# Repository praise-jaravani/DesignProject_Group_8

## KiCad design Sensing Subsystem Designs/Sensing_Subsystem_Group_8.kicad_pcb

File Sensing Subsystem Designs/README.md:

# Sensing Subsystem Designs - Micro-Mouse Project

## Overview
This directory contains all the necessary design files for the Sensing Subsystem of the Micro-Mouse Project. It includes PCB design files, production resources such as bill of materials (BOM) and Gerber files for manufacturing the final design. The purpose of this subsystem is to enable the micro-mouse to detect obstacles within the maze environment effectively.

## File Structure

### `/Sensing Subsystem Designs/`
- **README.md**: This document, detailing the file structure and purpose of each item.
- **Sensing_Subsystem_Group_8.kicad_pcb**: KiCad PCB design file for the sensing subsystem.
- **Sensing_Subsystem_Group_8.kicad_prl**: KiCad project local file, storing project-specific settings.
- **Sensing_Subsystem_Group_8.kicad_pro**: KiCad project file, which contains setup and configuration for the sensing subsystem project.
- **Sensing_Subsystem_Group_8.kicad_sch**: KiCad schematic file for the sensing subsystem.
- **sym-lib-table**: KiCad symbol library table file, listing all symbol libraries used in the project.

### `/Production Resources/`
- Contains BOM and Gerber files necessary for the production of the sensing subsystem. These are critical for manufacturing and assembly of the designed PCB.

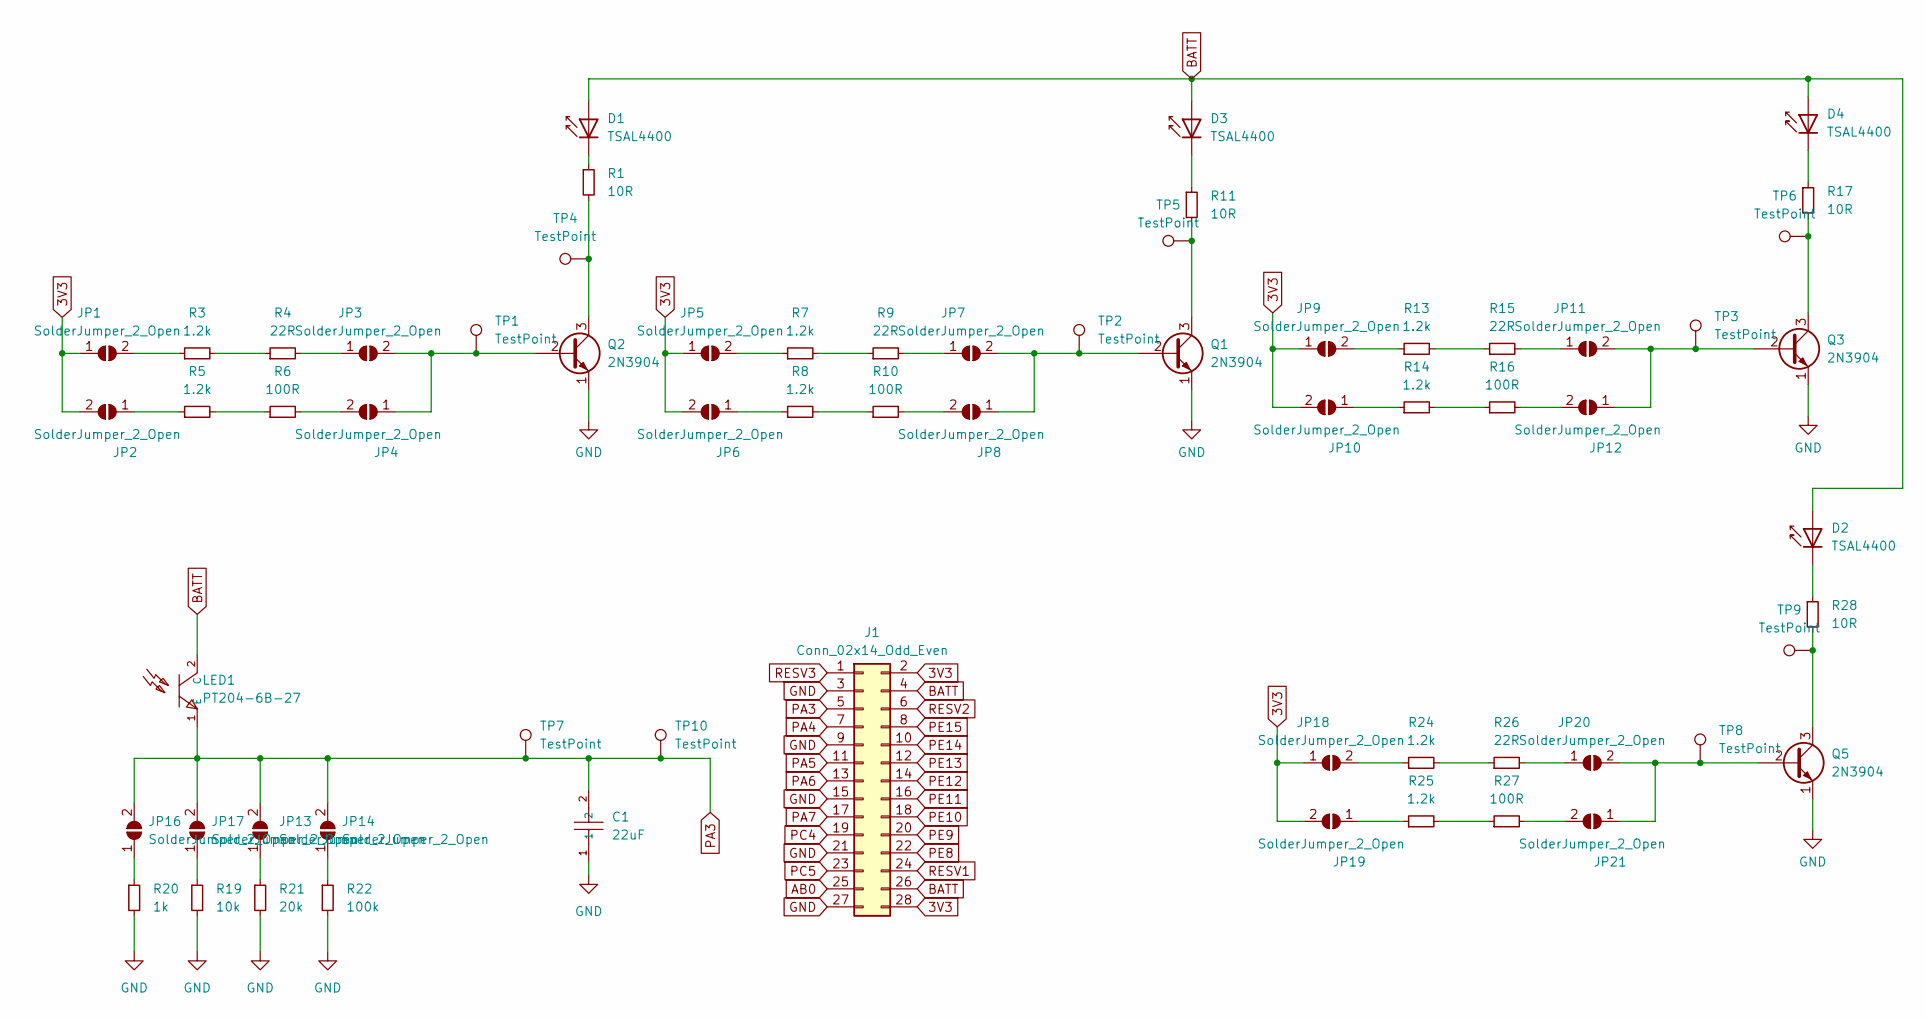
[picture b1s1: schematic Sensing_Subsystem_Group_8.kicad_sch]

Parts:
C1: 22uF; C0805; LCSC C45783
D1, D2, D3, D4: TSAL4400; LED_D3.0mm_IRBlack
J1: Conn_02x14_Odd_Even; PinHeader_2x14_P2.54mm_Vertical
JP1, JP2, JP3, JP4, JP5, JP6, JP7, JP8, JP9, JP10, JP11, JP12, JP13, JP14, JP16, JP17, JP18, JP19, JP20, JP21: SolderJumper_2_Open; SolderJumper-2_P1.3mm_Bridged2Bar_Pad1.0x1.5mm
LED1: PT204-6B-27; LED-TH_BD4.0-P2.54-RD; LCSC C142324
Q1, Q2, Q3, Q5: 2N3904; TO-92_Inline
R1, R11, R17, R28: 10R; R_0201_0603Metric
R3, R5, R7, R8, R13, R14, R24, R25: 1.2k; R_0201_0603Metric
R4, R9, R15, R26: 22R; R_0201_0603Metric
R6, R10, R16, R27: 100R; R_0201_0603Metric
R19: 10k; R_0201_0603Metric
R20: 1k; R_0201_0603Metric
R21: 20k; R_0201_0603Metric
R22: 100k; R_0201_0603Metric
TP1, TP2, TP3, TP4, TP5, TP6, TP7, TP8, TP9, TP10: TestPoint; TestPoint_2Pads_Pitch2.54mm_Drill0.8mm

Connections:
3V3: J1.2, J1.28, JP1.1 (A), JP2.2 (B), JP5.1 (A), JP6.2 (B), JP9.1 (A), JP10.2 (B), JP18.1 (A), JP19.2 (B)
AB0: J1.25
BATT: D1.2 (A), D2.2 (A), D3.2 (A), D4.2 (A), J1.4, J1.26, LED1.2 (C)
GND: C1.1, J1.3, J1.9, J1.15, J1.21, J1.27, Q1.1 (E), Q2.1 (E), Q3.1 (E), Q5.1 (E), R19.2, R20.2, R21.2, R22.2
unnamed: D1.1 (K), R1.1
unnamed: D2.1 (K), R28.1
unnamed: D3.1 (K), R11.1
unnamed: D4.1 (K), R17.1
unnamed: JP1.2 (B), R3.1
unnamed: JP2.1 (A), R5.1
unnamed: JP3.1 (A), R4.2
unnamed: JP3.2 (B), JP4.1 (A), Q2.2 (B), TP1.1
unnamed: JP4.2 (B), R6.2
unnamed: JP5.2 (B), R7.1
unnamed: JP6.1 (A), R8.1
unnamed: JP7.1 (A), R9.2
unnamed: JP7.2 (B), JP8.1 (A), Q1.2 (B), TP2.1
unnamed: JP8.2 (B), R10.2
unnamed: JP9.2 (B), R13.1
unnamed: JP10.1 (A), R14.1
unnamed: JP11.1 (A), R15.2
unnamed: JP11.2 (B), JP12.1 (A), Q3.2 (B), TP3.1
unnamed: JP12.2 (B), R16.2
unnamed: JP13.1 (A), R21.1
unnamed: JP14.1 (A), R22.1
unnamed: JP16.1 (A), R20.1
unnamed: JP17.1 (A), R19.1
unnamed: JP18.2 (B), R24.1
unnamed: JP19.1 (A), R25.1
unnamed: JP20.1 (A), R26.2
unnamed: JP20.2 (B), JP21.1 (A), Q5.2 (B), TP8.1
unnamed: JP21.2 (B), R27.2
unnamed: Q1.3 (C), R11.2, TP5.1
unnamed: Q2.3 (C), R1.2, TP4.1
unnamed: Q3.3 (C), R17.2, TP6.1
unnamed: Q5.3 (C), R28.2, TP9.1
unnamed: R3.2, R4.1
unnamed: R5.2, R6.1
unnamed: R7.2, R9.1
unnamed: R8.2, R10.1
unnamed: R13.2, R15.1
unnamed: R14.2, R16.1
unnamed: R24.2, R26.1
unnamed: R25.2, R27.1
PA3: C1.2, J1.5, JP13.2 (B), JP14.2 (B), JP16.2 (B), JP17.2 (B), LED1.1 (E), TP7.1, TP10.1
PA4: J1.7
PA5: J1.11
PA6: J1.13
PA7: J1.17
PC4: J1.19
PC5: J1.23
PE8: J1.22
PE9: J1.20
PE10: J1.18
PE11: J1.16
PE12: J1.14
PE13: J1.12
PE14: J1.10
PE15: J1.8
RESV1: J1.24
RESV2: J1.6
RESV3: J1.1

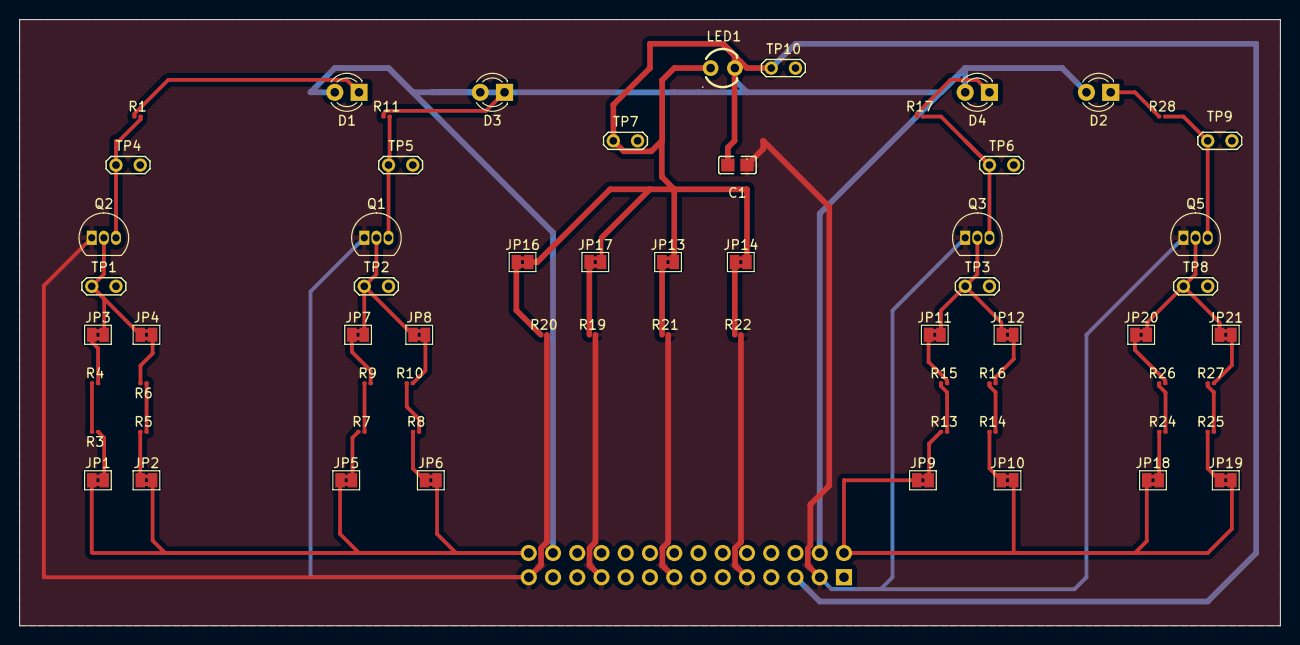
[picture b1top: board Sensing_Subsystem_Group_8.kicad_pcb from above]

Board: 2 copper layers, 132.1 x 63.5 mm, 65 parts (1 on the bottom side), 44 nets.

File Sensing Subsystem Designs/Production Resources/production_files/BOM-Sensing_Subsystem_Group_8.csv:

Comment,Designator,Footprint,LCSC
2N3904,"Q1,Q2,Q3,Q5",TO-92_Inline,C118538
PT204-6B-27,LED1,LED-TH_BD4.0-P2.54-RD,C142324
22uF,C1,C0805,C45783
TestPoint,TP9,TestPoint_2Pads_Pitch2.54mm_Drill0.8mm,
TestPoint,TP8,TestPoint_2Pads_Pitch2.54mm_Drill0.8mm,
10R,R28,R_0201_0603Metric,
100R,R27,R_0201_0603Metric,
22R,R26,R_0201_0603Metric,
1.2k,R25,R_0201_0603Metric,
1.2k,R24,R_0201_0603Metric,
SolderJumper_2_Open,JP21,SolderJumper-2_P1.3mm_Bridged2Bar_Pad1.0x1.5mm,
SolderJumper_2_Open,JP20,SolderJumper-2_P1.3mm_Bridged2Bar_Pad1.0x1.5mm,
SolderJumper_2_Open,JP19,SolderJumper-2_P1.3mm_Bridged2Bar_Pad1.0x1.5mm,
SolderJumper_2_Open,JP18,SolderJumper-2_P1.3mm_Bridged2Bar_Pad1.0x1.5mm,
TSAL4400,D2,LED_D3.0mm_IRBlack,
TestPoint,TP7,TestPoint_2Pads_Pitch2.54mm_Drill0.8mm,
TestPoint,TP6,TestPoint_2Pads_Pitch2.54mm_Drill0.8mm,
TestPoint,TP5,TestPoint_2Pads_Pitch2.54mm_Drill0.8mm,
TestPoint,TP4,TestPoint_2Pads_Pitch2.54mm_Drill0.8mm,
TestPoint,TP3,TestPoint_2Pads_Pitch2.54mm_Drill0.8mm,
TestPoint,TP2,TestPoint_2Pads_Pitch2.54mm_Drill0.8mm,
TestPoint,TP1,TestPoint_2Pads_Pitch2.54mm_Drill0.8mm,
100k,R22,R_0201_0603Metric,
20k,R21,R_0201_0603Metric,
1k,R20,R_0201_0603Metric,
10k,R19,R_0201_0603Metric,
10R,R17,R_0201_0603Metric,
100R,R16,R_0201_0603Metric,
22R,R15,R_0201_0603Metric,
1.2k,R14,R_0201_0603Metric,
1.2k,R13,R_0201_0603Metric,
10R,R11,R_0201_0603Metric,
100R,R10,R_0201_0603Metric,
22R,R9,R_0201_0603Metric,
1.2k,R8,R_0201_0603Metric,
1.2k,R7,R_0201_0603Metric,
100R,R6,R_0201_0603Metric,
1.2k,R5,R_0201_0603Metric,
22R,R4,R_0201_0603Metric,
1.2k,R3,R_0201_0603Metric,
10R,R1,R_0201_0603Metric,
SolderJumper_2_Open,JP17,SolderJumper-2_P1.3mm_Bridged2Bar_Pad1.0x1.5mm,
SolderJumper_2_Open,JP16,SolderJumper-2_P1.3mm_Bridged2Bar_Pad1.0x1.5mm,
SolderJumper_2_Open,JP14,SolderJumper-2_P1.3mm_Bridged2Bar_Pad1.0x1.5mm,
SolderJumper_2_Open,JP13,SolderJumper-2_P1.3mm_Bridged2Bar_Pad1.0x1.5mm,
SolderJumper_2_Open,JP12,SolderJumper-2_P1.3mm_Bridged2Bar_Pad1.0x1.5mm,
SolderJumper_2_Open,JP11,SolderJumper-2_P1.3mm_Bridged2Bar_Pad1.0x1.5mm,
SolderJumper_2_Open,JP10,SolderJumper-2_P1.3mm_Bridged2Bar_Pad1.0x1.5mm,
SolderJumper_2_Open,JP9,SolderJumper-2_P1.3mm_Bridged2Bar_Pad1.0x1.5mm,
SolderJumper_2_Open,JP8,SolderJumper-2_P1.3mm_Bridged2Bar_Pad1.0x1.5mm,
SolderJumper_2_Open,JP7,SolderJumper-2_P1.3mm_Bridged2Bar_Pad1.0x1.5mm,
SolderJumper_2_Open,JP6,SolderJumper-2_P1.3mm_Bridged2Bar_Pad1.0x1.5mm,
SolderJumper_2_Open,JP5,SolderJumper-2_P1.3mm_Bridged2Bar_Pad1.0x1.5mm,
SolderJumper_2_Open,JP4,SolderJumper-2_P1.3mm_Bridged2Bar_Pad1.0x1.5mm,
SolderJumper_2_Open,JP3,SolderJumper-2_P1.3mm_Bridged2Bar_Pad1.0x1.5mm,
SolderJumper_2_Open,JP2,SolderJumper-2_P1.3mm_Bridged2Bar_Pad1.0x1.5mm,
SolderJumper_2_Open,JP1,SolderJumper-2_P1.3mm_Bridged2Bar_Pad1.0x1.5mm,
TSAL4400,D4,LED_D3.0mm_IRBlack,
TSAL4400,D3,LED_D3.0mm_IRBlack,
TSAL4400,D1,LED_D3.0mm_IRBlack,
TestPoint,TP10,TestPoint_2Pads_Pitch2.54mm_Drill0.8mm,

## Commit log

2024-03-13 created new repo
2024-04-21 Updated File Structure
